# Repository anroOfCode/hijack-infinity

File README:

This is the home for the project to change the MSP430 on the hijack board to the new MSP430FR5969 fram based MSP

Wooo!

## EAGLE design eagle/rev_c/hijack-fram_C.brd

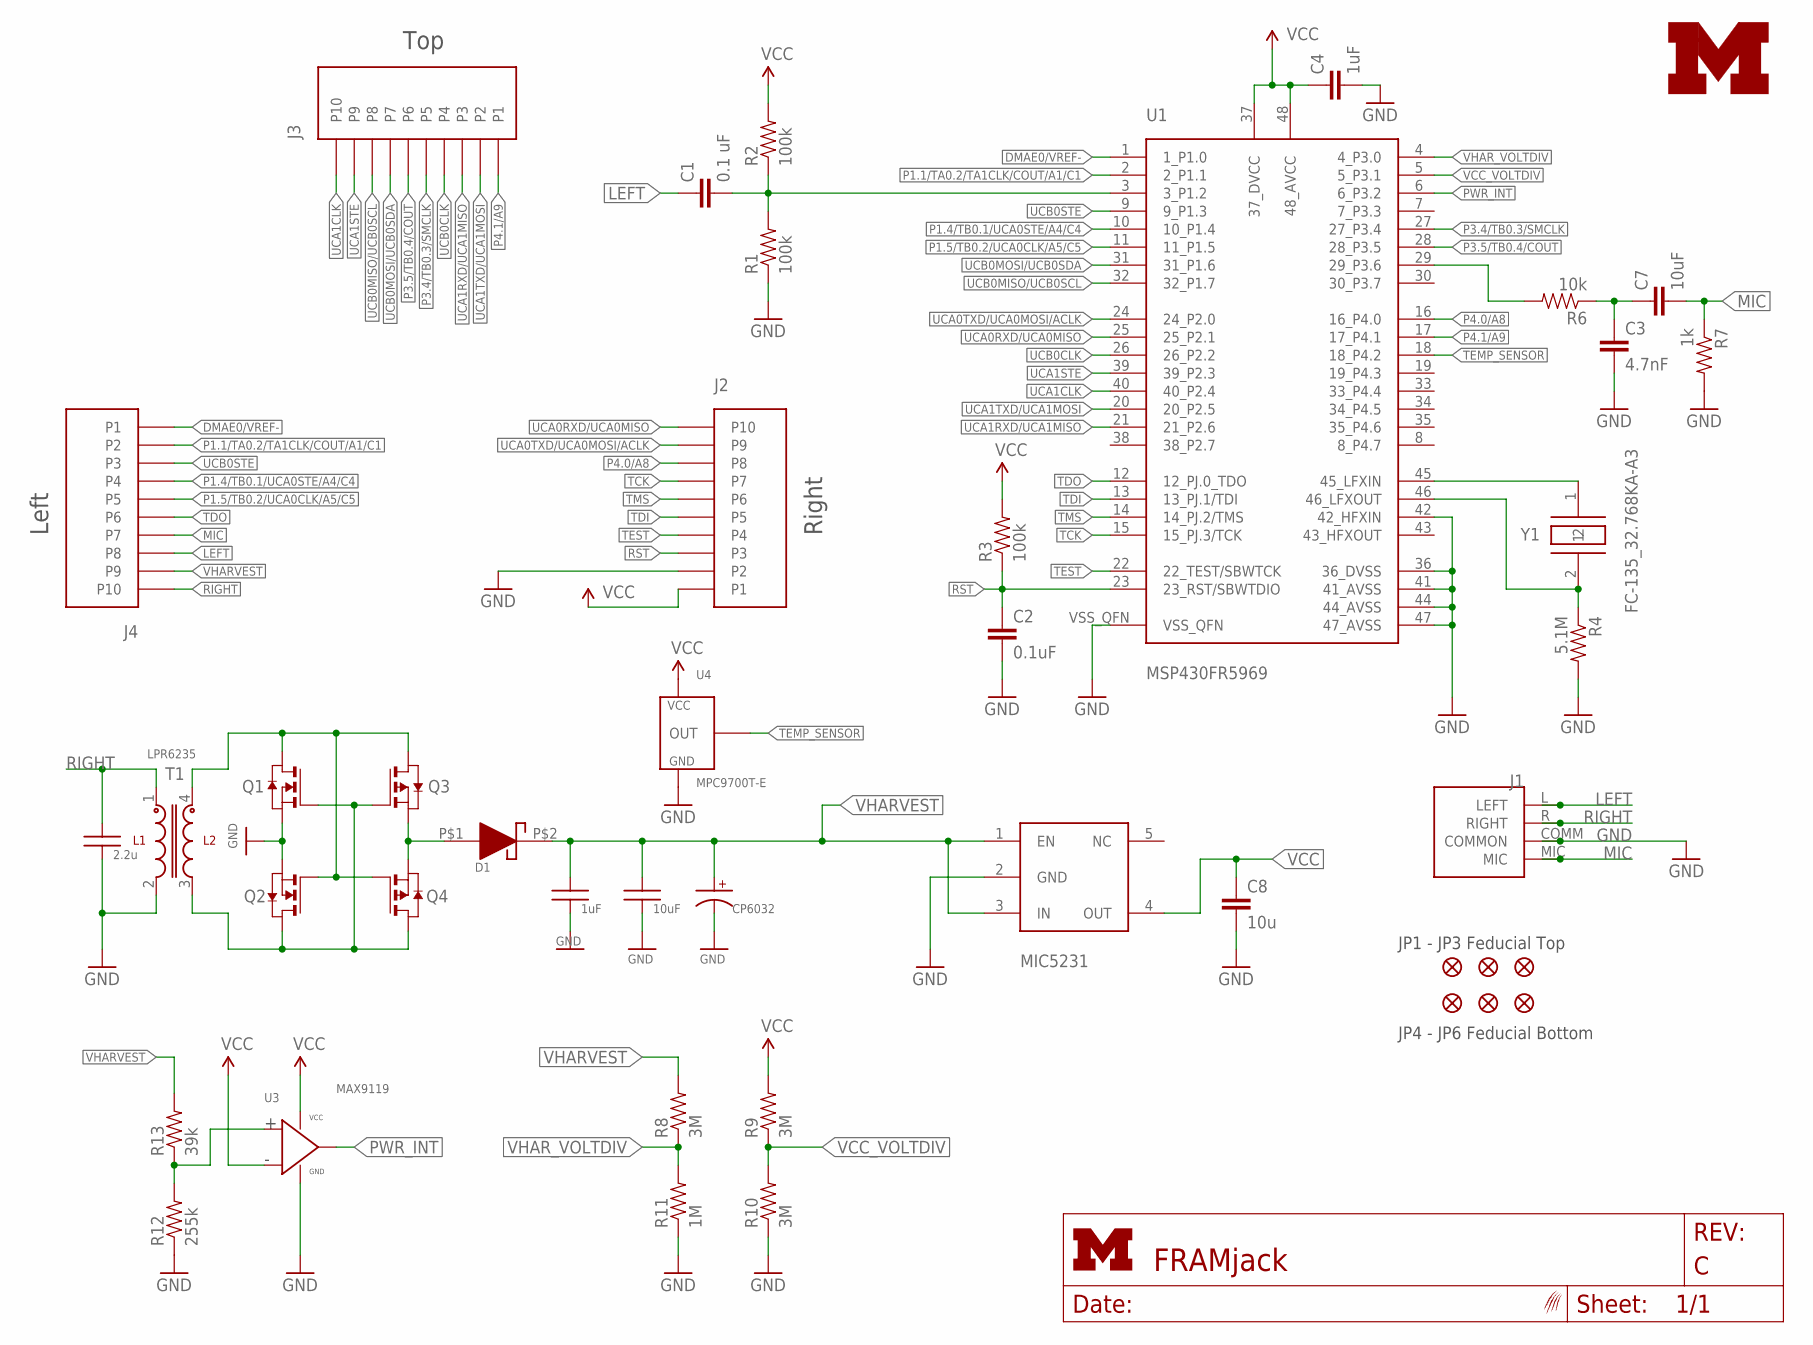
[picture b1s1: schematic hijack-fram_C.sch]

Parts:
C1: 0.1 uF; 0603-CAP
C2: 0.1uF; 0603-CAP
C3: 4.7nF; 0603-CAP
C4: 1uF; 0603-CAP
C5: 1uF; C0603
C6: 10uF; C0603
C7: 10uF; 0603-CAP
C8: 10u; C0603
C9: CP6032; CT6032
C10: 2.2u; C0603
D1: B5818WS-SCHOTTKY-DIODE; SOD-323
J1: 3.5JACK4CONNSUNSTONE_QUICKTURN; PLUGBOARDCONNECTOR_SUNSTONE
J2, J3, J4: HEADER10POS; 10PIN2MMHEADER
JP1, JP2, JP3, JP4, JP5, JP6: FIDUCIAL1X2; FIDUCIAL-1X2
Q1, Q2: NMOSSOT23; SOT-23
Q3, Q4: PMOSSOT23; SOT-23
R1, R2, R3: 100k; 0603-RES
R4: 5.1M; 0603-RES
R6: 10k; 0603-RES
R7: 1k; 0603-RES
R8, R9, R10: 3M; 0603-RES
R11: 1M; 0603-RES
R12: 255k; 0603-RES
R13: 39k; 0603-RES
T1: LPR6235
U1: MSP430FR5969; RGZ(S-PQFP-N48)
U2: MIC5231; SOT23-5
U3: MAX9119; SC70-5
U4: MPC9700T-E; SOT-23
U$1: WOLVERINE
U$4: UMICH_SOLID_SMALL; UMICH_SOLID_75MIL
Y1: FC-135_32.768KA-A3; FC-135

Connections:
DMAE0/VREF-: J4.P1, U1.1 (1_P1.0)
GND: C2.2, C3.2, C4.2, C5.2, C6.2, C8.2, C9.-, C10.2, J1.COMM (COMMON), J2.P2, Q1.2 (S), Q2.2 (S), R1.1, R4.2, R7.2, R10.1, R11.1, R12.1, T1.2, U1.36 (36_DVSS), U1.41 (41_AVSS), U1.42 (42_HFXIN), U1.44 (44_AVSS), U1.47 (47_AVSS), U1.VSS_QFN, U2.2 (GND), U3.2 (GND), U4.GND
LEFT: C1.1, J1.L (LEFT), J4.P8
MIC: C7.2, J1.MIC, J4.P7, R7.1
unnamed: C1.2, R1.2, R2.1, U1.3 (3_P1.2)
unnamed: R4.1, U1.46 (46_LFXOUT), Y1.2
unnamed: R6.2, U1.29 (29_P3.6)
unnamed: R12.2, R13.1, U3.3 (IN+)
unnamed: U1.45 (45_LFXIN), Y1.1
unnamed: Q1.1 (D), Q2.3 (G), Q3.1 (D), Q4.3 (G), T1.4
unnamed: Q1.3 (G), Q2.1 (D), Q3.3 (G), Q4.1 (D), T1.3
unnamed: C3.1, C7.1, R6.1
unnamed: D1.P$1 (A), Q3.2 (S), Q4.2 (S)
P1.1/TA0.2/TA1CLK/COUT/A1/C1: J4.P2, U1.2 (2_P1.1)
P1.4/TB0.1/UCA0STE/A4/C4: J4.P4, U1.10 (10_P1.4)
P1.5/TB0.2/UCA0CLK/A5/C5: J4.P5, U1.11 (11_P1.5)
P3.4/TB0.3/SMCLK: J3.P5, U1.27 (27_P3.4)
P3.5/TB0.4/COUT: J3.P6, U1.28 (28_P3.5)
P4.0/A8: J2.P8, U1.16 (16_P4.0)
P4.1/A9: J3.P1, U1.17 (17_P4.1)
PWR_INT: U1.6 (6_P3.2), U3.1 (OUT)
RIGHT: C10.1, J1.R (RIGHT), J4.P10, T1.1
RST: C2.1, J2.P3, R3.1, U1.23 (23_RST/SBWTDIO)
TCK: J2.P7, U1.15 (15_PJ.3/TCK)
TDI: J2.P5, U1.13 (13_PJ.1/TDI)
TDO: J4.P6, U1.12 (12_PJ.0_TDO)
TEMP_SENSOR: U1.18 (18_P4.2), U4.VOUT (OUT)
TEST: J2.P4, U1.22 (22_TEST/SBWTCK)
TMS: J2.P6, U1.14 (14_PJ.2/TMS)
UCA0RXD/UCA0MISO: J2.P10, U1.25 (25_P2.1)
UCA0TXD/UCA0MOSI/ACLK: J2.P9, U1.24 (24_P2.0)
UCA1CLK: J3.P10, U1.40 (40_P2.4)
UCA1RXD/UCA1MISO: J3.P3, U1.21 (21_P2.6)
UCA1STE: J3.P9, U1.39 (39_P2.3)
UCA1TXD/UCA1MOSI: J3.P2, U1.20 (20_P2.5)
UCB0CLK: J3.P4, U1.26 (26_P2.2)
UCB0MISO/UCB0SCL: J3.P8, U1.32 (32_P1.7)
UCB0MOSI/UCB0SDA: J3.P7, U1.31 (31_P1.6)
UCB0STE: J4.P3, U1.9 (9_P1.3)
VCC: C4.1, C8.1, J2.P1, R2.2, R3.2, R9.2, U1.37 (37_DVCC), U1.48 (48_AVCC), U2.4 (OUT), U3.4 (IN-), U3.5 (VCC), U4.VDD (VCC)
VCC_VOLTDIV: R9.1, R10.2, U1.5 (5_P3.1)
VHARVEST: C5.1, C6.1, C9.+, D1.P$2 (C), J4.P9, R8.2, R13.2, U2.1 (EN), U2.3 (IN)
VHAR_VOLTDIV: R8.1, R11.2, U1.4 (4_P3.0)

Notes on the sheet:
Left
Top
Right
JP1 - JP3 Feducial Top
JP4 - JP6 Feducial Bottom

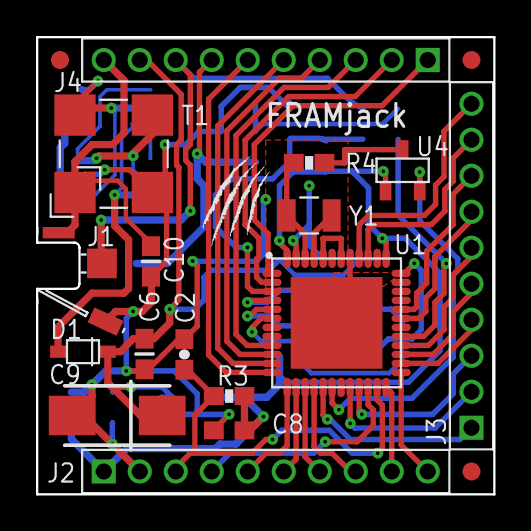
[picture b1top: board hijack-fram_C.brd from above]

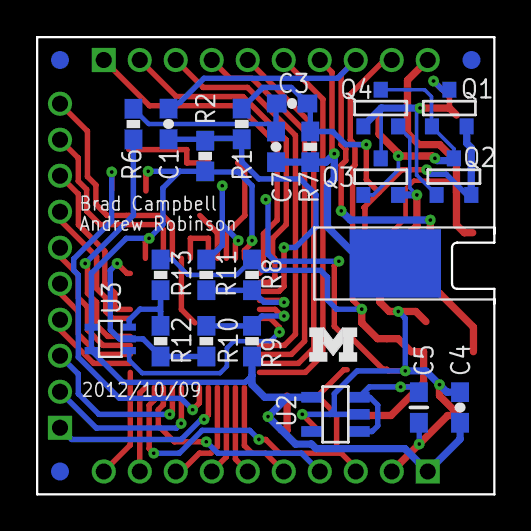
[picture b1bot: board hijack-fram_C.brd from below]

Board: 2 copper layers, 25.4 x 25.4 mm, 45 parts (25 on the bottom side), 43 nets.

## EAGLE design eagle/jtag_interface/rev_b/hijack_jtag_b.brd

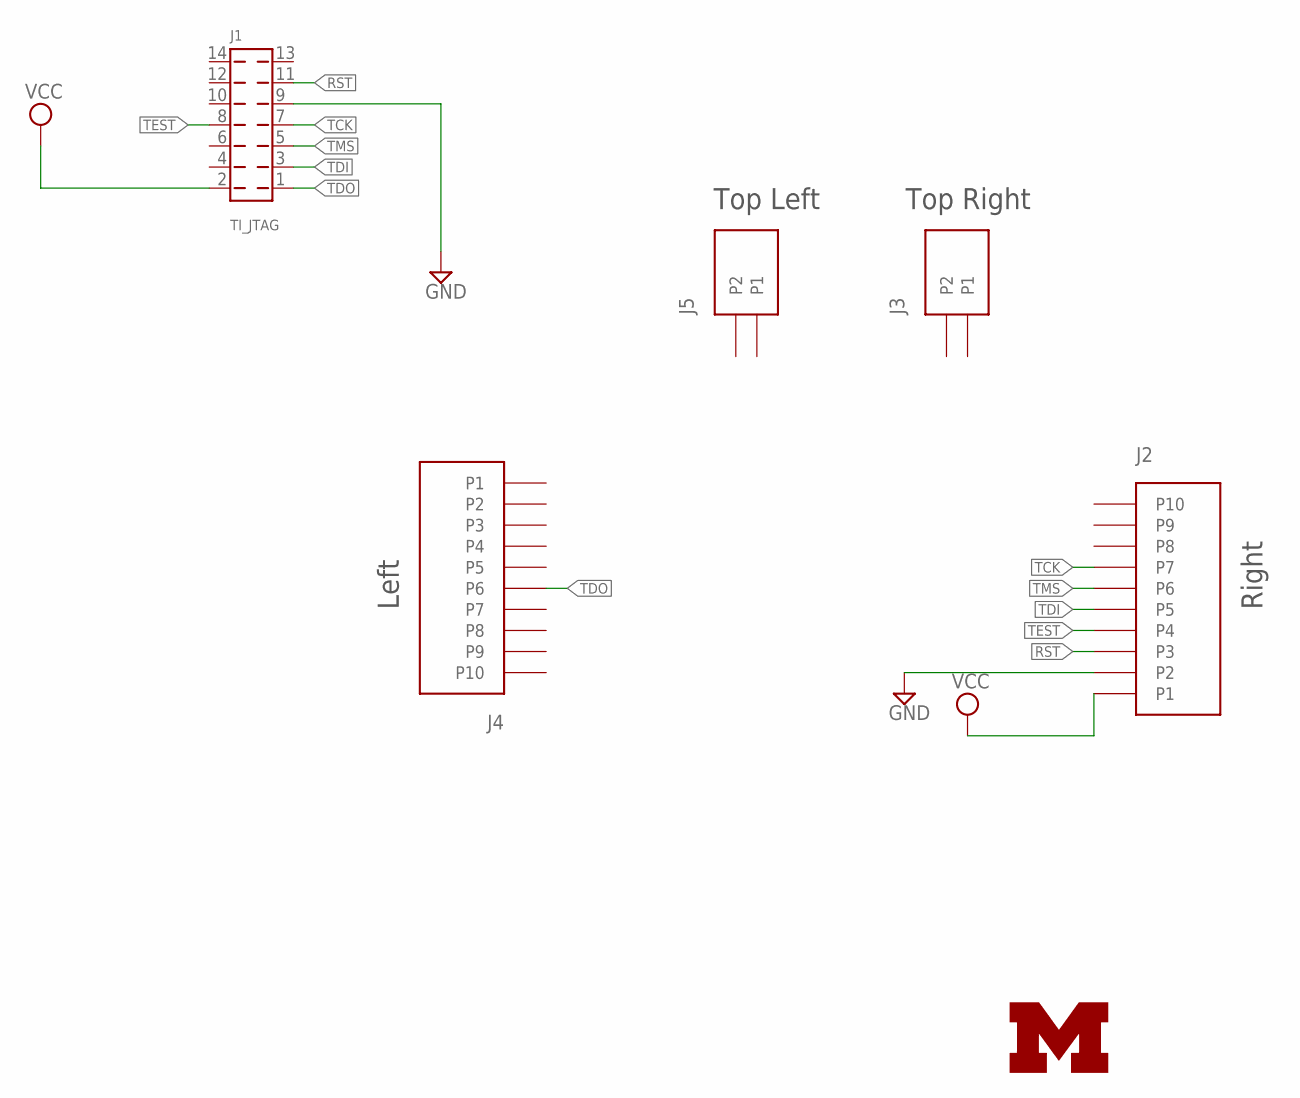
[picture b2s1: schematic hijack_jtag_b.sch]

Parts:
J1: TI_JTAG; TST-107
J2, J4: HEADER10POS; 10PIN2MMHEADER
J3, J5: HEADER2POS; 2PIN2MMHEADER
U$2: UMICH_SOLID

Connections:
GND: J1.9, J2.P2
RST: J1.11, J2.P3
TCK: J1.7, J2.P7
TDI: J1.3, J2.P5
TDO: J1.1, J4.P6
TEST: J1.8, J2.P4
TMS: J1.5, J2.P6
VCC: J1.2, J2.P1

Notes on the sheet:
Left
Right
Top Left
Top Right

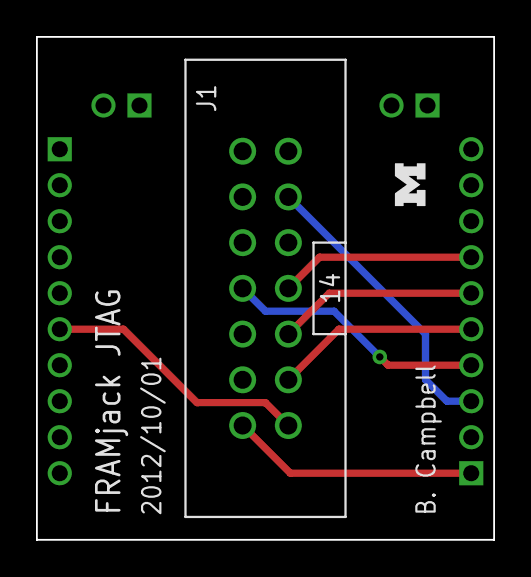
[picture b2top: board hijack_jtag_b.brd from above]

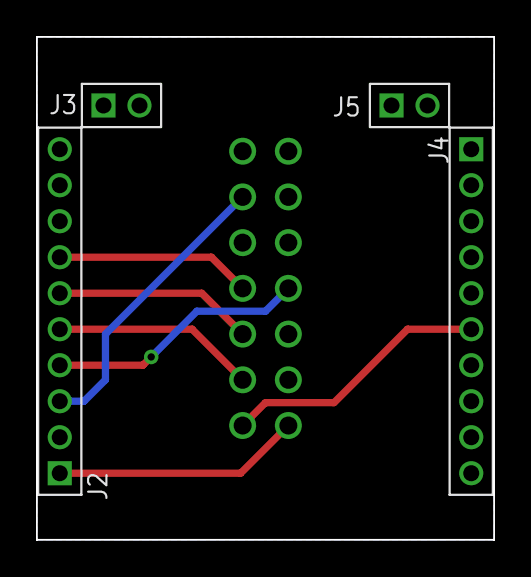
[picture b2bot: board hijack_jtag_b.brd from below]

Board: 2 copper layers, 25.4 x 27.9 mm, 6 parts (4 on the bottom side), 8 nets.

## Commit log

2012-10-18 Create gh-pages branch via GitHub
2012-10-22 Test commit
2012-10-22 Initial commit of hijack-infinity work.
2012-10-24 Refactored and continued work on refactoring PAL and adding support for msp430f1611
2012-11-15 small fix to framingEngine
2012-11-15 fixed up periphs
2012-11-15 adding some more information about the msp430f1611
2012-11-15 refactoring and building skeleton for msp430f1611 support
2012-11-21 bringing up msp430f1611 platform... testing bacic clock
2012-11-26 adding timer initialization code
2012-11-27 working version of f1611 port
2012-11-27 New readme.
2012-11-27 Here's a screenshot!
2012-11-27 optimization turned on... up to 100 B/s transmission
2012-12-06 Put code block in code tags in README.md
    So that Sam doesn't think -I is -l
2012-12-07 refactoring the android app into a library and app
2012-12-07 removed bin and gen directories
2012-12-07 adding frequency sweep app
2012-12-07 Frequency sweeping application created
